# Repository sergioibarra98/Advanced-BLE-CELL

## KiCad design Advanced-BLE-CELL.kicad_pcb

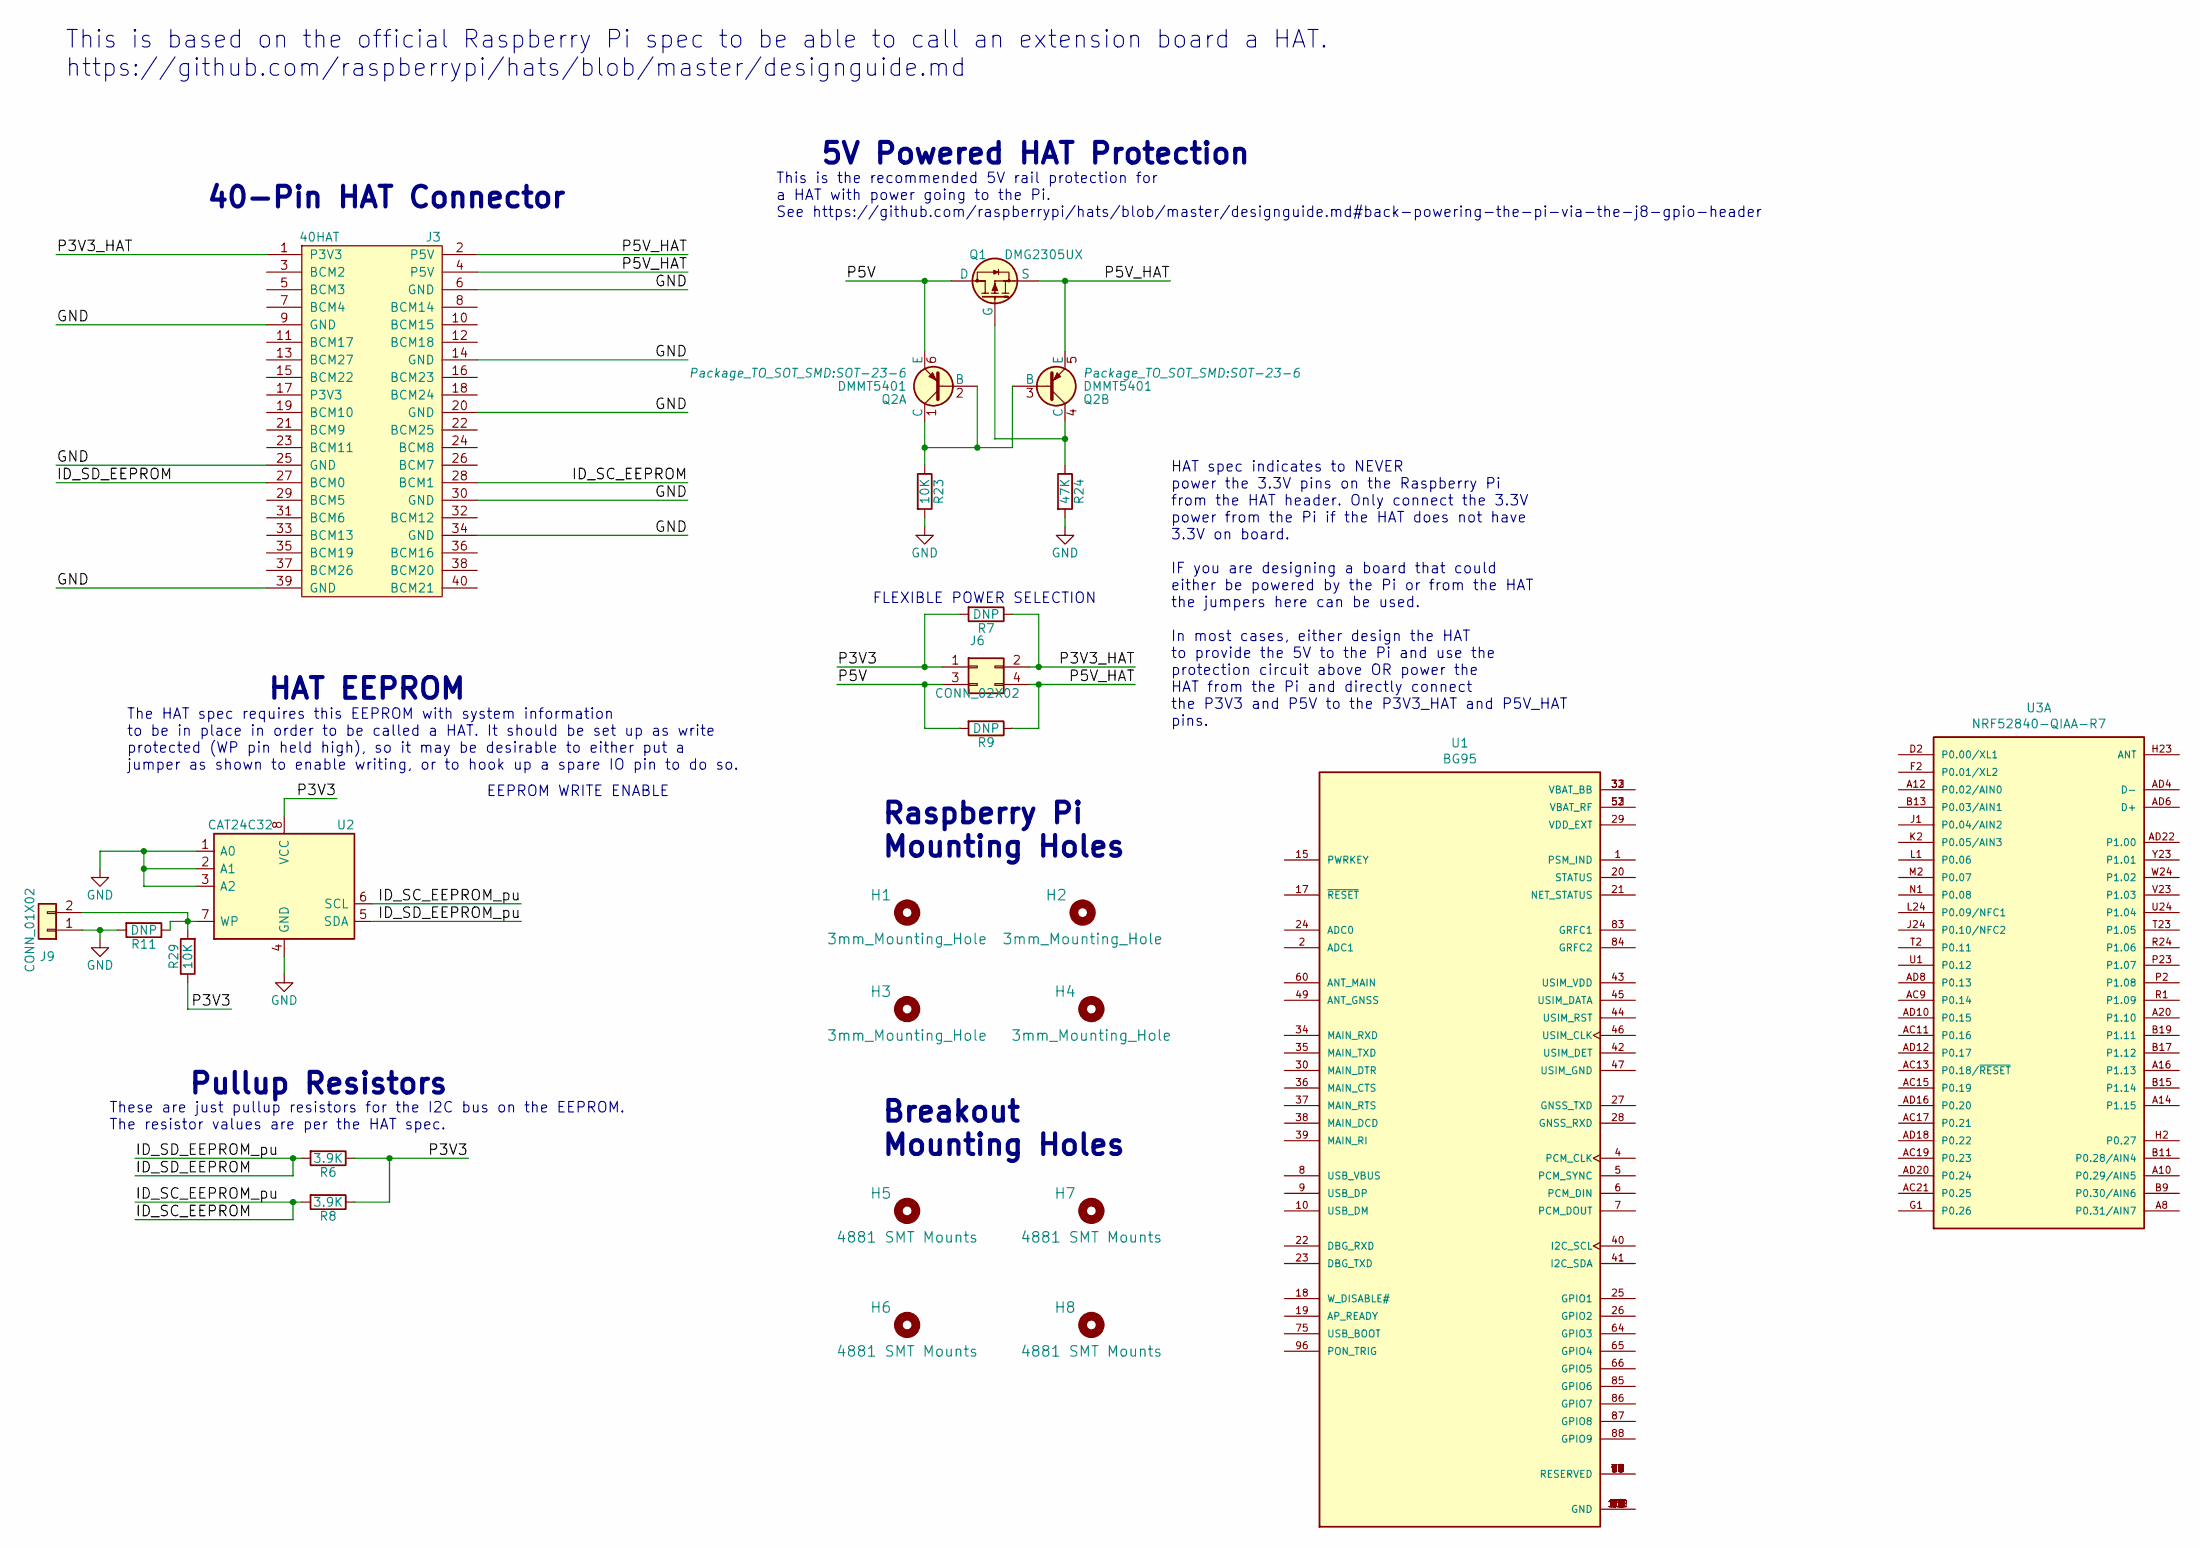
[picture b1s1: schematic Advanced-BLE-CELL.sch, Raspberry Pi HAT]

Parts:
H1, H2, H3, H4: 3mm_Mounting_Hole; NPTH_3mm_ID
H5, H6, H7, H8: 4881 SMT Mounts; 4881
J3: 40HAT; PinSocket_2x20_P2.54mm_Vertical
J6: CONN_02X02; PinHeader_2x02_P2.54mm_Vertical
J9: CONN_01X02; PinHeader_1x02_P2.54mm_Vertical
Q1: DMG2305UX; SOT-23
Q2: DMMT5401; SOT-23-6
R6, R8: 3.9K; R_0603_1608Metric_Pad0.84x1.00mm_HandSolder
R7, R9, R11: DNP; R_0603_1608Metric_Pad0.84x1.00mm_HandSolder
R23, R29: 10K; R_0603_1608Metric_Pad0.84x1.00mm_HandSolder
R24: 47K; R_0603_1608Metric_Pad0.84x1.00mm_HandSolder
U1: BG95; XCVR_BG95; PARTREV 1.1
U2: CAT24C32; SOIC-8_3.9x4.9mm_P1.27mm
U3: NRF52840-QIAA-R7; NORDIC_NRF52840-QIAA-R7

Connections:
/ID_SC_EEPROM: J3.28 (BCM1), R8.2, U2.6 (SCL)
/ID_SD_EEPROM: J3.27 (BCM0), R6.2, U2.5 (SDA)
/P3V3: J6.1, R6.1, R7.2, R8.1, R29.1, U2.8 (VCC)
/P3V3_HAT: J3.1 (P3V3), J6.2, R7.1
/P5V: J6.3, Q1.3 (D), Q2.6 (E), R9.2
/P5V_HAT: J3.2 (P5V), J3.4 (P5V), J6.4, Q1.2 (S), Q2.5 (E), R9.1
GND: J3.6 (GND), J3.9 (GND), J3.14 (GND), J3.20 (GND), J3.25 (GND), J3.30 (GND), J3.34 (GND), J3.39 (GND), J9.1, R11.2, R23.2, R24.2, U2.1 (A0), U2.2 (A1), U2.3 (A2), U2.4 (GND)
unnamed: J9.2, R11.1, R29.2, U2.7 (WP)
unnamed: Q1.1 (G), Q2.4 (C), R24.1
unnamed: Q2.1 (C), Q2.2 (B), Q2.3 (B), R23.1
unnamed: U1.11 (RESERVED), U1.12 (RESERVED), U1.13 (RESERVED), U1.14 (RESERVED), U1.16 (RESERVED), U1.51 (RESERVED), U1.56 (RESERVED), U1.57 (RESERVED), U1.63 (RESERVED), U1.76 (RESERVED), U1.77 (RESERVED), U1.78 (RESERVED), U1.92 (RESERVED), U1.93 (RESERVED), U1.94 (RESERVED), U1.95 (RESERVED), U1.97 (RESERVED), U1.98 (RESERVED), U1.99 (RESERVED)
unnamed: U1.32 (VBAT_BB), U1.33 (VBAT_BB)
unnamed: U1.52 (VBAT_RF), U1.53 (VBAT_RF)
unnamed: U1.3 (GND), U1.31 (GND), U1.48 (GND), U1.50 (GND), U1.54 (GND), U1.55 (GND), U1.58 (GND), U1.59 (GND), U1.61 (GND), U1.62 (GND), U1.67 (GND), U1.68 (GND), U1.69 (GND), U1.70 (GND), U1.71 (GND), U1.72 (GND), U1.73 (GND), U1.74 (GND), U1.79 (GND), U1.80 (GND), U1.81 (GND), U1.82 (GND), U1.89 (GND), U1.90 (GND), U1.91 (GND), U1.100 (GND), U1.101 (GND), U1.102 (GND)

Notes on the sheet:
FLEXIBLE POWER SELECTION
5V Powered HAT Protection
This is the recommended 5V rail protection for a HAT with power going to the Pi. See https://github.com/raspberrypi/hats/blob/master/designguide.md#back-powering-the-pi-via-the-j8-gpio-header
EEPROM WRITE ENABLE
Pullup Resistors
HAT EEPROM
Raspberry Pi Mounting Holes
40-Pin HAT Connector
HAT spec indicates to NEVER power the 3.3V pins on the Raspberry Pi from the HAT header. Only connect the 3.3V power from the Pi if the HAT does not have 3.3V on board. IF you are designing a board that could either be powered by the Pi or from the HAT the jumpers here can be used. In most cases, e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
The HAT spec requires this EEPROM with system information to be in place in order to be called a HAT. It should be set up as write protected (WP pin held high), so it may be desirable to either put a jumper as shown to enable writing, or to hook up a spare IO pin to do so.
These are just pullup resistors for the I2C bus on the EEPROM. The resistor values are per the HAT spec.
This is based on the official Raspberry Pi spec to be able to call an extension board a HAT. https://github.com/raspberrypi/hats/blob/master/designguide.md
Breakout Mounting Holes

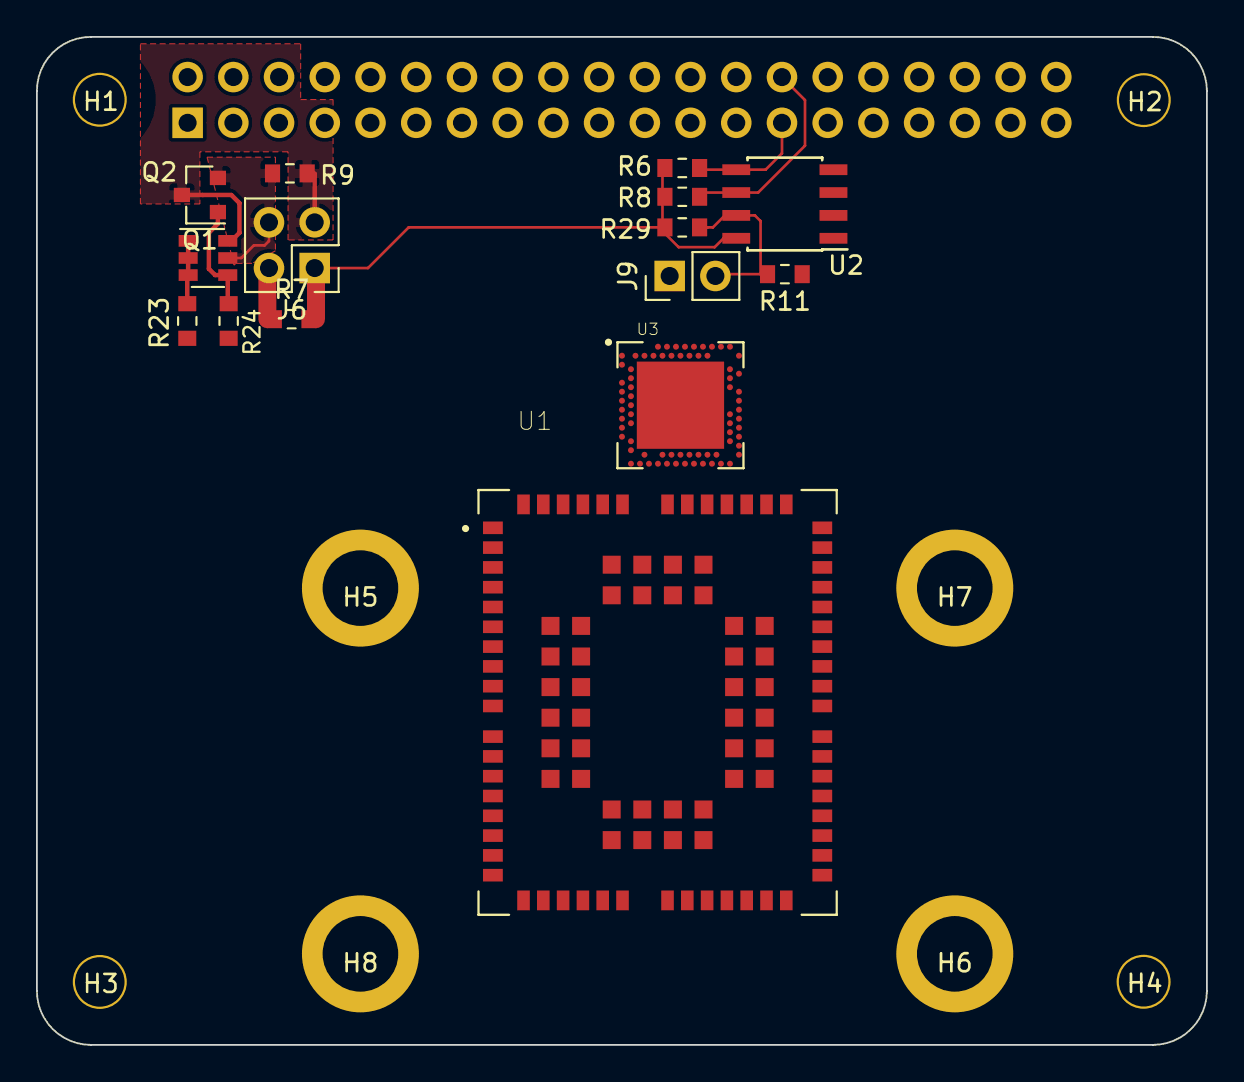
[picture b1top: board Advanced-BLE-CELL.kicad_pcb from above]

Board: 4 copper layers, 65.0 x 56.0 mm, 24 parts (1 on the bottom side), 14 nets.

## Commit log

2021-05-23 Added a new KiCad project
2021-05-23 Added .gitignore file
2021-05-23 Added Symbols & footprints for BG95, NRF52840 and 4881 breakout mounting holes
2021-05-23 Moved project to Design folder & Added Datasheet folder
2021-05-23 Added Stand-Alone Power Management/bq24650 datasheet
